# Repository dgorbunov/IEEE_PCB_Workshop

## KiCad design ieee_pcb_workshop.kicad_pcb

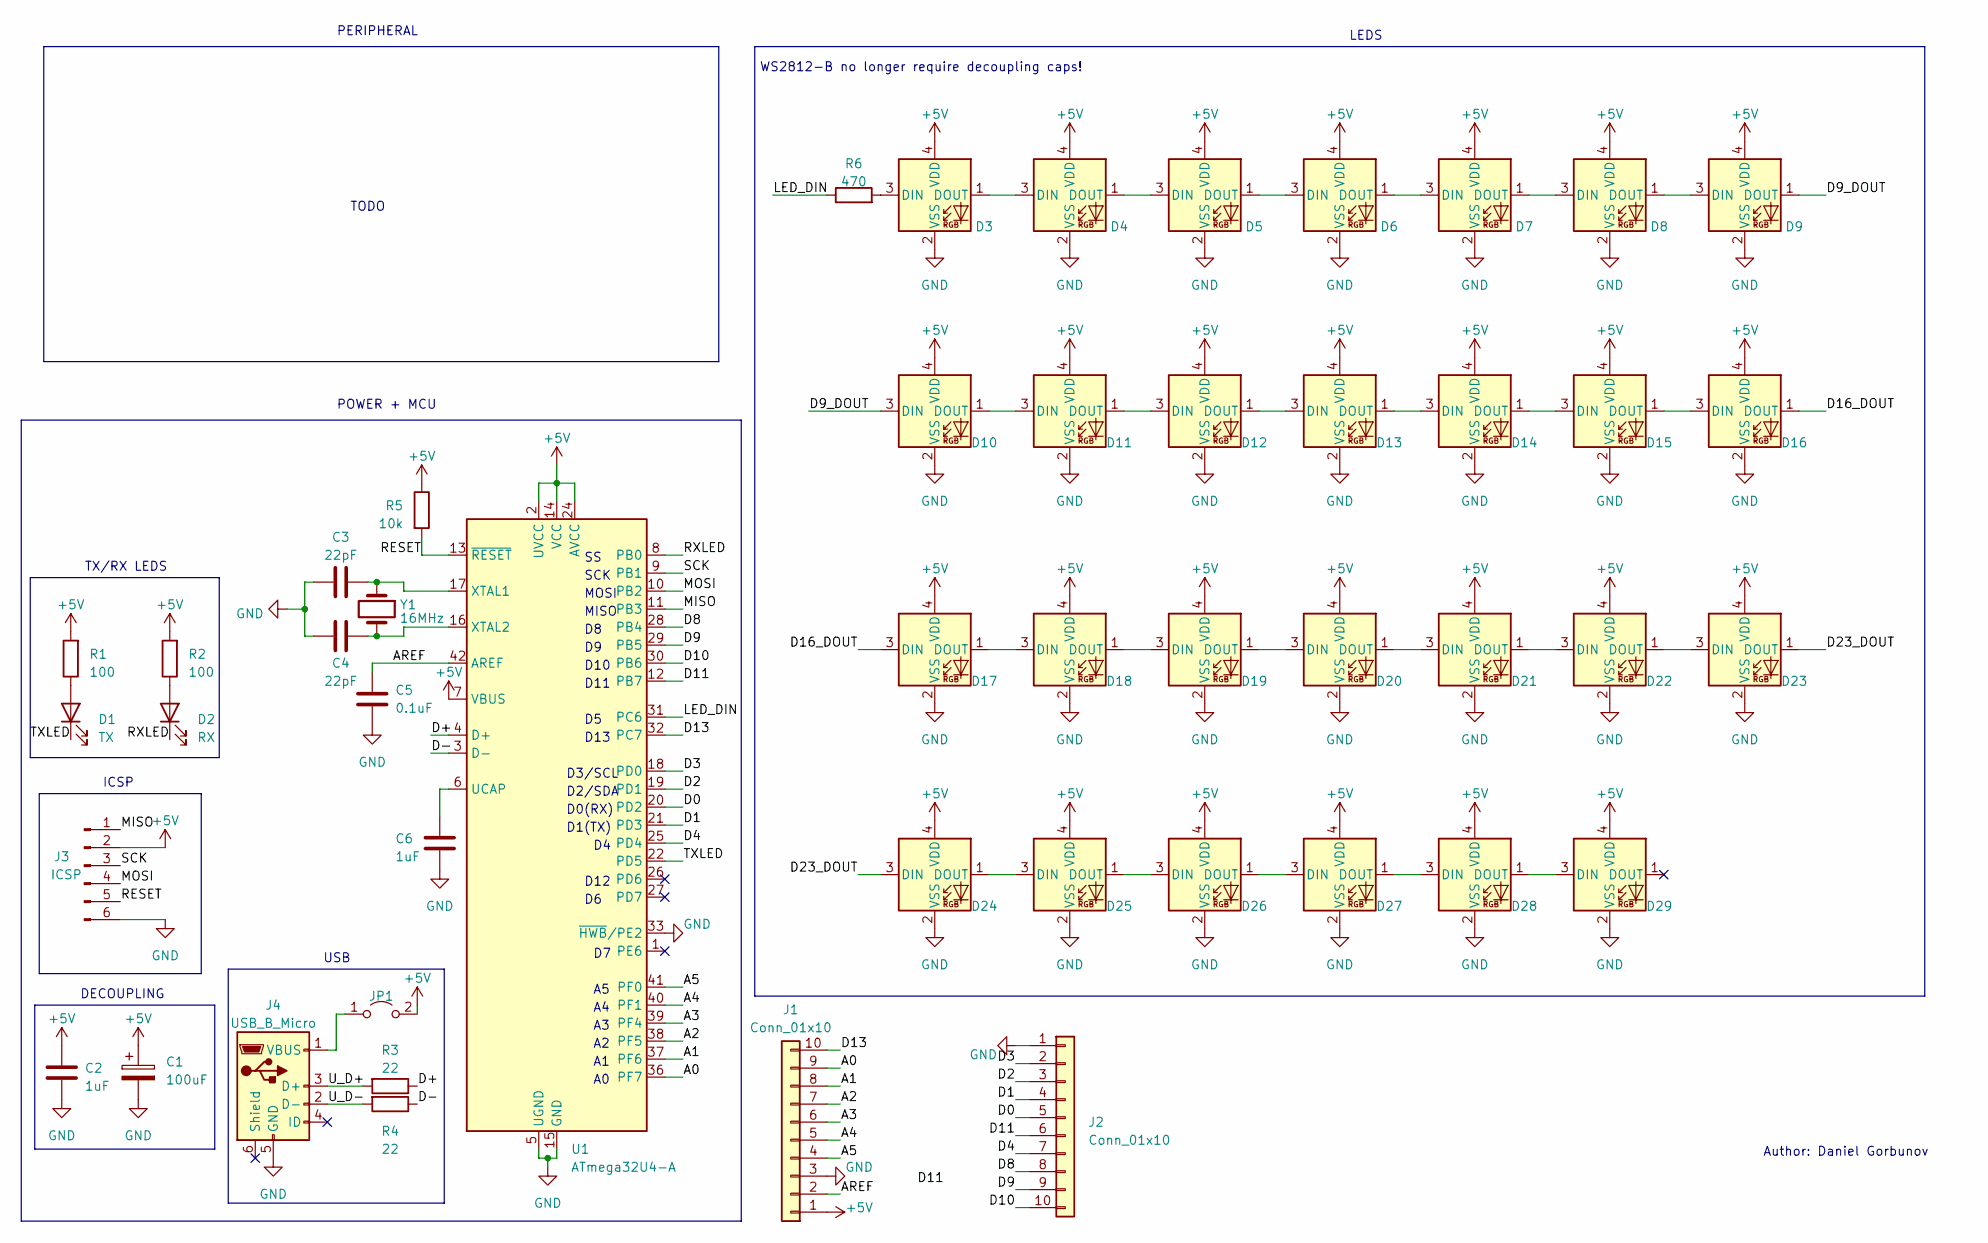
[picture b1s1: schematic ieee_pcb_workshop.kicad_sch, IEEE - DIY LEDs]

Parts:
C1: 100uF; CP_Elec_5x5.3
C2, C6: 1uF; C_0805_2012Metric_Pad1.18x1.45mm_HandSolder
C3, C4: 22pF; C_0805_2012Metric_Pad1.18x1.45mm_HandSolder
C5: 0.1uF; C_0805_2012Metric_Pad1.18x1.45mm_HandSolder
D1: TX; LED_0805_2012Metric_Pad1.15x1.40mm_HandSolder
D2: RX; LED_0805_2012Metric_Pad1.15x1.40mm_HandSolder
D3, D4, D5, D6, D7, D8, D9, D10, D11, D12, D13, D14, D15, D16, D17, D18, D19, D20, D21, D22, D23, D24, D25, D26, D27, D28, D29: SK6812MINI; LED_SK6812MINI_PLCC4_3.5x3.5mm_P1.75mm
J1, J2: Conn_01x10; PinHeader_1x10_P2.54mm_Vertical
J3: ICSP; PinHeader_2x03_P2.54mm_Vertical
J4: USB_B_Micro; USB_Micro-B_GCT_USB3076-30-A
JP1: Jumper_2_Open; SolderJumper-2_P1.3mm_Open_TrianglePad1.0x1.5mm
R1, R2: 100; R_0805_2012Metric_Pad1.20x1.40mm_HandSolder
R3, R4: 22; R_0805_2012Metric_Pad1.20x1.40mm_HandSolder
R5: 10k; R_0805_2012Metric_Pad1.20x1.40mm_HandSolder
R6: 470; R_0805_2012Metric_Pad1.20x1.40mm_HandSolder
U1: ATmega32U4-A; TQFP-44_10x10mm_P0.8mm
Y1: 16MHz; Crystal_SMD_5032-2Pin_5.0x3.2mm

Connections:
+5V: C1.1, C2.1, D3.4 (VDD), D4.4 (VDD), D5.4 (VDD), D6.4 (VDD), D7.4 (VDD), D8.4 (VDD), D9.4 (VDD), D10.4 (VDD), D11.4 (VDD), D12.4 (VDD), D13.4 (VDD), D14.4 (VDD), D15.4 (VDD), D16.4 (VDD), D17.4 (VDD), D18.4 (VDD), D19.4 (VDD), D20.4 (VDD), D21.4 (VDD), D22.4 (VDD), D23.4 (VDD), D24.4 (VDD), D25.4 (VDD), D26.4 (VDD), D27.4 (VDD), D28.4 (VDD), D29.4 (VDD), J1.1, J3.2, JP1.2 (B), R1.2, R2.2, R5.1, U1.2 (UVCC), U1.7 (VBUS), U1.14 (VCC), U1.24 (AVCC), U1.34 (VCC), U1.44 (AVCC)
/A0: J1.9, U1.36 (PF7)
/A1: J1.8, U1.37 (PF6)
/A2: J1.7, U1.38 (PF5)
/A3: J1.6, U1.39 (PF4)
/A4: J1.5, U1.40 (PF1)
/A5: J1.4, U1.41 (PF0)
/AREF: C5.1, J1.2, U1.42 (AREF)
/D0: J2.5, U1.20 (PD2)
/D1: J2.4, U1.21 (PD3)
/D2: J2.3, U1.19 (PD1)
/D3: J2.2, U1.18 (PD0)
/D4: J2.7, U1.25 (PD4)
/D8: J2.8, U1.28 (PB4)
/D9: J2.9, U1.29 (PB5)
/D9_DOUT: D9.1 (DOUT), D10.3 (DIN)
/D10: J2.10, U1.30 (PB6)
/D11: J2.6, U1.12 (PB7)
/D13: J1.10, U1.32 (PC7)
/D16_DOUT: D16.1 (DOUT), D17.3 (DIN)
/D23_DOUT: D23.1 (DOUT), D24.3 (DIN)
/D+: R3.1, U1.4 (D+)
/D-: R4.1, U1.3 (D-)
/LED_DIN: R6.1, U1.31 (PC6)
/MISO: J3.1, U1.11 (PB3)
/MOSI: J3.4, U1.10 (PB2)
/RESET: J3.5, R5.2, U1.13 (~RESET)
/RXLED: D2.1 (K), U1.8 (PB0)
/SCK: J3.3, U1.9 (PB1)
/TXLED: D1.1 (K), U1.22 (PD5)
/U_D+: J4.3 (D+), R3.2
/U_D-: J4.2 (D-), R4.2
GND: C1.2, C2.2, C3.2, C4.2, C5.2, C6.2, D3.2 (VSS), D4.2 (VSS), D5.2 (VSS), D6.2 (VSS), D7.2 (VSS), D8.2 (VSS), D9.2 (VSS), D10.2 (VSS), D11.2 (VSS), D12.2 (VSS), D13.2 (VSS), D14.2 (VSS), D15.2 (VSS), D16.2 (VSS), D17.2 (VSS), D18.2 (VSS), D19.2 (VSS), D20.2 (VSS), D21.2 (VSS), D22.2 (VSS), D23.2 (VSS), D24.2 (VSS), D25.2 (VSS), D26.2 (VSS), D27.2 (VSS), D28.2 (VSS), D29.2 (VSS), J1.3, J2.1, J3.6, J4.5 (GND), U1.5 (UGND), U1.15 (GND), U1.23 (GND), U1.33 (~HWB/PE2), U1.35 (GND), U1.43 (GND)
unnamed: D1.2 (A), R1.1
unnamed: D2.2 (A), R2.1
unnamed: D3.3 (DIN), R6.2
unnamed: D3.1 (DOUT), D4.3 (DIN)
unnamed: D4.1 (DOUT), D5.3 (DIN)
unnamed: D5.1 (DOUT), D6.3 (DIN)
unnamed: D6.1 (DOUT), D7.3 (DIN)
unnamed: D7.1 (DOUT), D8.3 (DIN)
unnamed: D8.1 (DOUT), D9.3 (DIN)
unnamed: D10.1 (DOUT), D11.3 (DIN)
unnamed: D11.1 (DOUT), D12.3 (DIN)
unnamed: D12.1 (DOUT), D13.3 (DIN)
unnamed: D13.1 (DOUT), D14.3 (DIN)
unnamed: D14.1 (DOUT), D15.3 (DIN)
unnamed: D15.1 (DOUT), D16.3 (DIN)
unnamed: D17.1 (DOUT), D18.3 (DIN)
unnamed: D18.1 (DOUT), D19.3 (DIN)
unnamed: D19.1 (DOUT), D20.3 (DIN)
unnamed: D20.1 (DOUT), D21.3 (DIN)
unnamed: D21.1 (DOUT), D22.3 (DIN)
unnamed: D22.1 (DOUT), D23.3 (DIN)
unnamed: D24.1 (DOUT), D25.3 (DIN)
unnamed: D25.1 (DOUT), D26.3 (DIN)
unnamed: D26.1 (DOUT), D27.3 (DIN)
unnamed: D27.1 (DOUT), D28.3 (DIN)
unnamed: D28.1 (DOUT), D29.3 (DIN)
unnamed: J4.1 (VBUS), JP1.1 (A)
unnamed: C6.1, U1.6 (UCAP)
unnamed: C3.1, U1.17 (XTAL1), Y1.1
unnamed: C4.1, U1.16 (XTAL2), Y1.2

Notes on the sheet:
MOSI
D2/SDA
LEDS
D11
D3/SCL
USB
DECOUPLING
D1(TX)
D13
TODO
WS2812-B no longer require decoupling caps!
Author: Daniel Gorbunov
MISO
D10
POWER + MCU
TX/RX LEDS
ICSP
SCK
D12
D0(RX)
PERIPHERAL

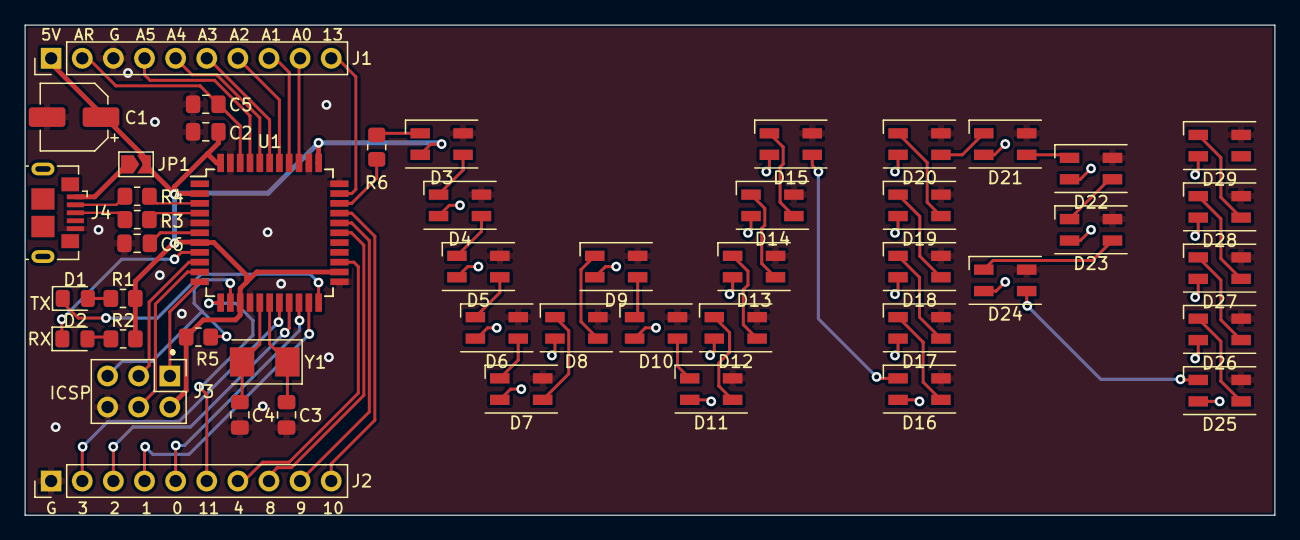
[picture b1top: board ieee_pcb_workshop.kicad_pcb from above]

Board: 2 copper layers, 102.0 x 40.0 mm, 48 parts (0 on the bottom side), 63 nets.

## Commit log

2024-03-27 add 01 lecture
2024-03-28 added outline.md, worked on slides
2024-03-28 added images
2024-03-29 day 1 slides
2024-03-29 gitignore
2024-03-29 remove key
2024-03-29 add readme
2024-03-29 reorg
2024-03-29 rm images
2024-03-29 rm images for real
2024-03-29 remove fab0
2024-03-29 update key
2024-04-04 lecture 2 files
2024-04-04 kicad files
2024-04-05 add lecture 2
2024-04-05 lecture 2 slides
2024-04-16 add starter code
2024-04-16 add flashlight code
